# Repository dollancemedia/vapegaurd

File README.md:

# VapeGuard - Real-time Vape Detection System

A comprehensive IoT-based vape detection system using ESP32-C6, machine learning, and real-time monitoring.

## 🏗️ Architecture

```
┌─────────────┐    WiFi     ┌─────────────┐    HTTP/WS   ┌─────────────┐
│   ESP32-C6  │ ──────────► │   Backend   │ ────────────► │  Frontend   │
│   Sensors   │             │  (FastAPI)  │              │   (React)   │
└─────────────┘             └─────────────┘              └─────────────┘
                                    │
                                    ▼
                            ┌─────────────┐
                            │  MongoDB    │
                            │   Atlas     │
                            └─────────────┘
                                    │
                                    ▼
                            ┌─────────────┐
                            │  XGBoost    │
                            │ ML Model    │
                            └─────────────┘
```

## 🚀 Features

### Hardware (ESP32-C6)
- **Multi-sensor Detection**: MQ-2 smoke sensor, DHT22 temperature/humidity, air quality sensor
- **WiFi Connectivity**: Real-time data transmission
- **Local Alerts**: LED and buzzer notifications
- **Zigbee Ready**: ESP32-C6 supports Zigbee mesh networking (future feature)
- **Low Power**: Optimized for continuous operation

### Backend (FastAPI + MongoDB)
- **Real-time API**: RESTful endpoints for sensor data
- **Machine Learning**: XGBoost model for vape detection
- **Data Storage**: MongoDB Atlas for scalable data storage
- **WebSocket Support**: Real-time updates to frontend
- **Vercel Deployment**: Serverless deployment ready

### Frontend (React)
- **Real-time Dashboard**: Live sensor readings and alerts
- **Device Management**: Monitor and control ESP32 devices
- **Event History**: Track and analyze detection events
- **Responsive Design**: Works on desktop and mobile
- **Vercel Deployment**: Static site deployment ready

### Machine Learning
- **XGBoost Model**: High-accuracy vape detection
- **Feature Engineering**: Advanced sensor data processing
- **Real-time Inference**: Sub-second prediction times
- **Confidence Scoring**: Reliability metrics for each prediction

## 📁 Project Structure

```
vape-project/
├── backend/                 # FastAPI backend
│   ├── app/
│   │   ├── main.py         # FastAPI application
│   │   ├── config.py       # Configuration settings
│   │   ├── models/         # Data models
│   │   ├── routers/        # API endpoints
│   │   └── ml/             # Machine learning models
│   └── requirements.txt    # Python dependencies
├── frontend/               # React frontend
│   ├── src/
│   │   ├── components/     # React components
│   │   ├── pages/          # Page components
│   │   ├── services/       # API services
│   │   └── App.js          # Main application
│   ├── public/             # Static assets
│   └── package.json        # Node.js dependencies
├── esp32_vape_sensor/      # ESP32-C6 Arduino code
│   └── esp32_vape_sensor.ino
├── vercel.json             # Vercel deployment config
├── DEPLOYMENT_GUIDE.md     # Detailed deployment instructions
└── README.md               # This file
```

## 🛠️ Quick Start & Run Commands

### Prerequisites
- Node.js 16+ and npm
- Python 3.8+
- Arduino IDE with ESP32 support
- MongoDB (Running locally or via Atlas)

### 1. Start the Database
Ensure MongoDB is running.
- **Windows Service**: Usually runs automatically.
- **Manual**: Run `mongod` in a separate terminal.

### 2. Start the Backend
The backend **must** listen on `0.0.0.0` to accept connections from the ESP32.

```powershell
cd backend
python -m uvicorn app.main:app --reload --host 0.0.0.0 --port 8000
```
*   **Success Indicator**: Logs show `Uvicorn running on http://0.0.0.0:8000`.

### 3. Start the Frontend
Open a **new terminal**.

```powershell
cd frontend
$env:PORT=3002; npm start
```
*   **Success Indicator**: Browser opens to `http://localhost:3002`.

### 4. Power the ESP32
Plug in your ESP32. It is pre-configured to connect to your WiFi and send data to `10.0.0.43:8000`.

---

## 🔧 Hardware Setup
1. **Board**: Adafruit ESP32 Feather V2
2. **Connections**:
   - PMS5003 TX → ESP32 RX (GPIO 16)
   - PMS5003 RX → ESP32 TX (GPIO 17)
   - Power & Ground

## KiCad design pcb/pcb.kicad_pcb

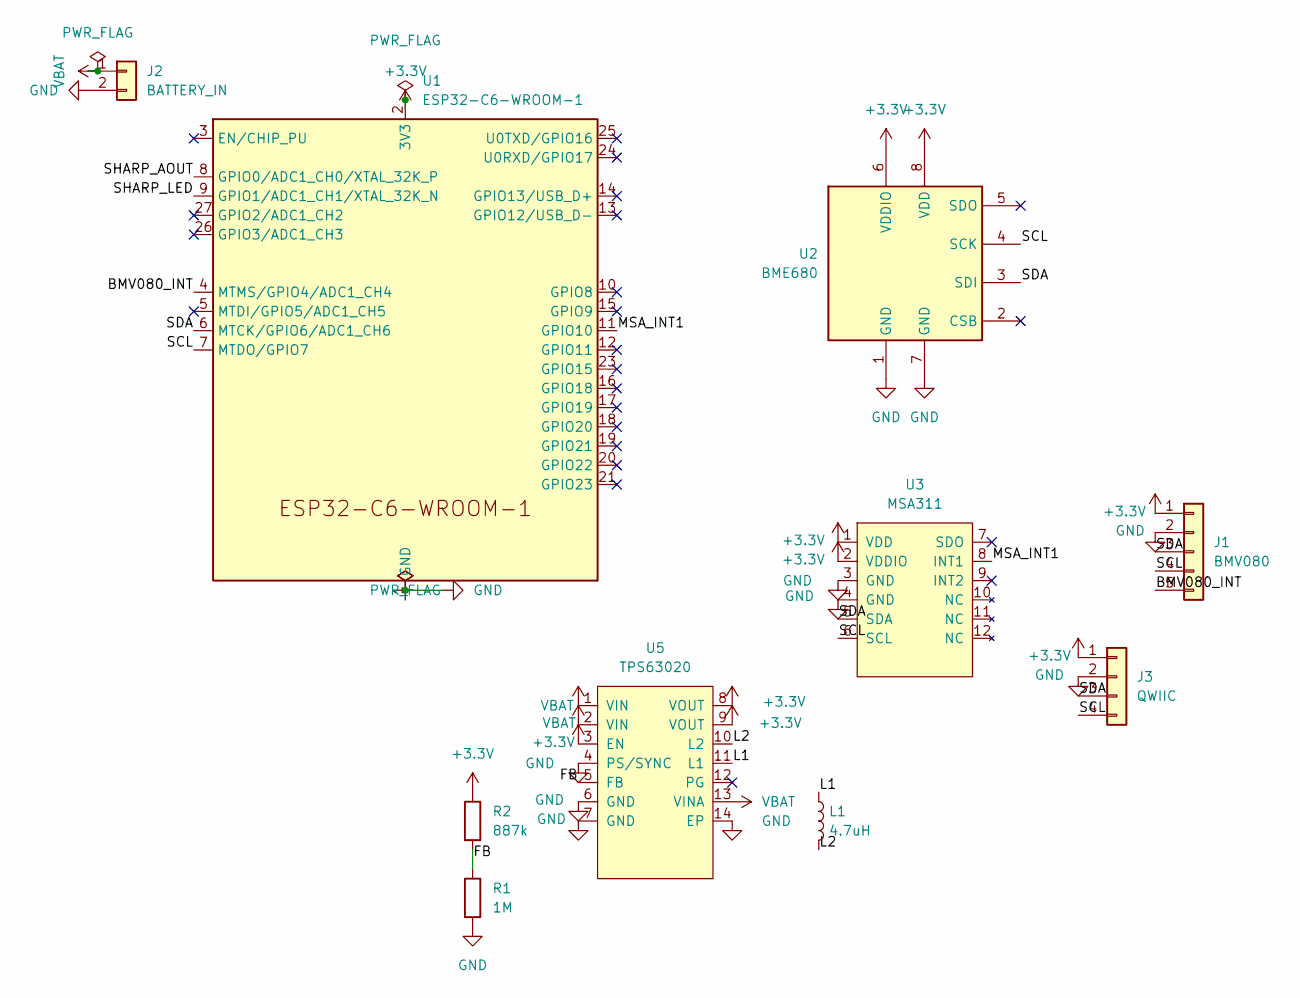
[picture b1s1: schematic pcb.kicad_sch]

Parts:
J1: BMV080; PinHeader_1x05_P2.54mm_Vertical
J2: BATTERY_IN; JST_PH_B2B-PH-K_1x02_P2.00mm_Vertical
J3: QWIIC; JST_SH_SM04B-SRSS-TB_1x04-1MP_P1.00mm_Horizontal
L1: 4.7uH; L_0402_1005Metric
R1: 1M; R_0402_1005Metric
R2: 887k; R_0402_1005Metric
U1: ESP32-C6-WROOM-1
U2: BME680; Bosch_LGA-8_3x3mm_P0.8mm_ClockwisePinNumbering
U3: MSA311; LGA-12_2x2mm_P0.5mm
U5: TPS63020; IC_TPS63020DSJT

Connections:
+3.3V: J1.1, J3.1, R2.1, U1.2 (3V3), U2.6 (VDDIO), U2.8 (VDD), U3.1 (VDD), U3.2 (VDDIO), U5.3 (EN), U5.8 (VOUT), U5.9 (VOUT)
/BMV080_INT: J1.5, U1.4 (MTMS/GPIO4/ADC1_CH4)
/FB: R1.1, R2.2, U5.5 (FB)
/L1: L1.1, U5.11 (L1)
/L2: L1.2, U5.10 (L2)
/MSA_INT1: U1.11 (GPIO10), U3.8 (INT1)
/SCL: J1.4, J3.4, U1.7 (MTDO/GPIO7), U2.4 (SCK), U3.6 (SCL)
/SDA: J1.3, J3.3, U1.6 (MTCK/GPIO6/ADC1_CH6), U2.3 (SDI), U3.5 (SDA)
/SHARP_AOUT: U1.8 (GPIO0/ADC1_CH0/XTAL_32K_P)
/SHARP_LED: U1.9 (GPIO1/ADC1_CH1/XTAL_32K_N)
GND: J1.2, J2.2, J3.2, R1.2, U1.1 (GND), U1.28 (GND), U1.29 (GND), U2.1 (GND), U2.7 (GND), U3.3 (GND), U3.4 (GND), U5.4 (PS/SYNC), U5.6 (GND), U5.7 (GND), U5.14 (EP)
VBAT: J2.1, U5.1 (VIN), U5.2 (VIN), U5.13 (VINA)

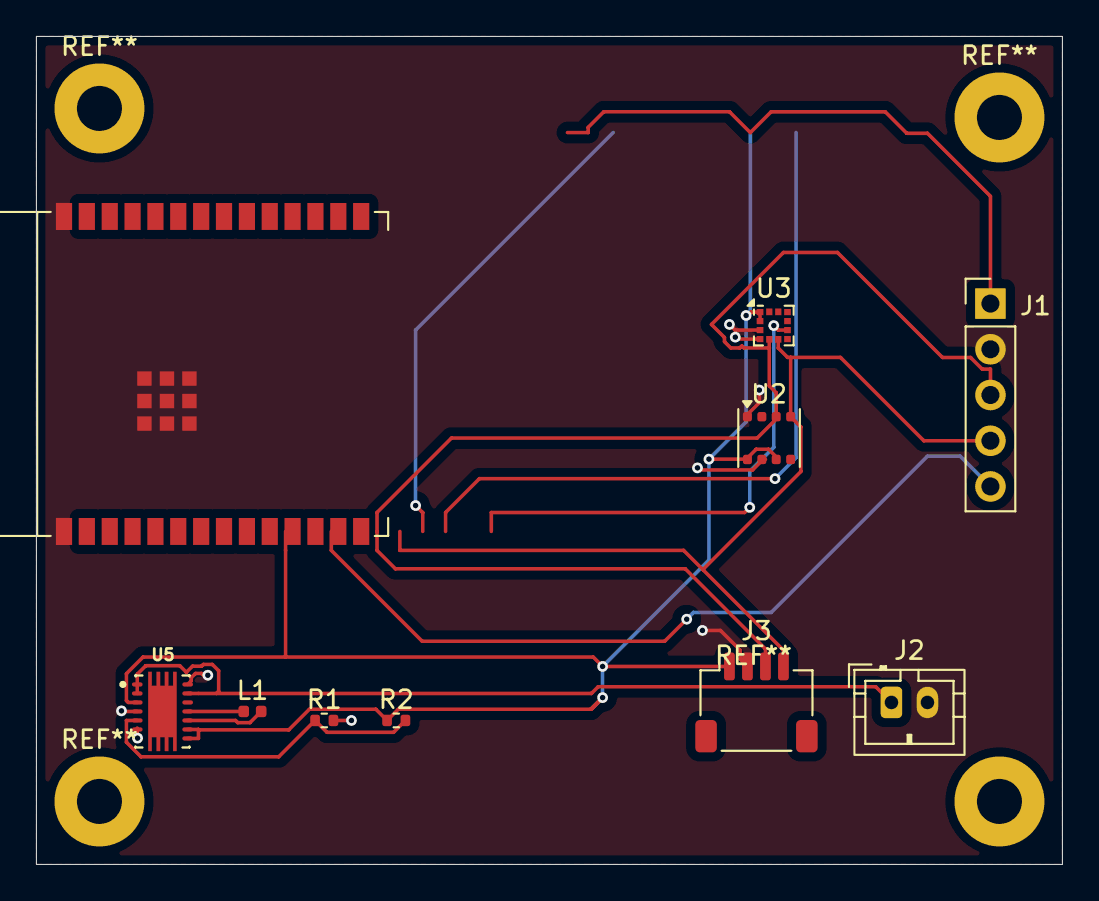
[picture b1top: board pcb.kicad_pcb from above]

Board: 2 copper layers, 57.0 x 46.0 mm, 10 parts (0 on the bottom side), 10 nets.

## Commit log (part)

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2025-07-31 second commit
2025-08-01 Archive old Express backend
2025-08-03 Fix model dump path and add serialized model
2025-08-04 Fix API port discrepancy between frontend and backend
2025-08-04 Add device summary endpoint and event feedback route
2025-08-24 Prepare for Vercel deployment: Add vercel.json, update frontend for env vars, add deployment scripts
2025-08-24 Fix MongoDB environment variables in vercel.json for deployment
2025-08-24 Fix ESLint warnings and errors - remove unused variables and imports, fix missing dependencies
2025-08-24 Fix Vercel deployment configuration - remove duplicate vercel.json and fix routing
2025-08-29 Update ESP32 vape sensor project with PMS5003 integration, hardware guides, and Arduino tools
2025-12-28 feat: prepare for deployment - backend auth, frontend clerk integration, and vercel config
2025-12-28 Fix: Add vercel.json and rename proxy.ts to middleware.ts
2025-12-30 chore: prepare backend for deployment and update config
2025-12-30 fix: delay db connection in train_model.py to prevent import-time crash
2025-12-30 update landingpage submodule to include login redirect
2025-12-30 Update dashboard to dynamically load campus map based on user (wwhs/irvington)
2025-12-30 Remove Trae Solo watermark and update login redirect
2025-12-31 Update DeviceMap with organization-based map selection and asset reorganization
2025-12-31 Update project files: Sync local changes to remote
2025-12-31 Update CORS to include Railway production domain
2025-12-31 fix: make MONGODB_URI optional to prevent startup crash
2025-12-31 chore: update backend config and add nixpacks.toml
2025-12-31 Update repository: Flatten landingpage submodule and remove debris
2025-12-31 feat: update favicon to tablogo.png
2025-12-31 feat: enhance ui with smoother animations and updated content
2026-01-01 Update model_config and esp32_vape_sensor sketch
2026-01-01 Update esp32_vape_sensor_002 sketch
2026-01-01 Fix Dashboard: Add missing useAuth import and correct DeviceMap data source
2026-01-01 Refactor Dashboard WebSocket connection to prevent infinite reconnection loop
2026-01-01 Fix WebSocket infinite loop by memoizing entire options object including protocols
2026-01-01 Apply user fixes to useWebSocket hook
2026-01-01 pls work bro
2026-01-01 pls work 2x
2026-01-01 Update mobile dashboard: Full-width map, remove footer, improve hooks compliance
2026-01-01 Resolve merge conflicts and apply mobile dashboard updates
2026-01-01 Refactor school selection and map image logic
    Updated components to use organization name instead of slug for school selection and map image paths. DeviceMap now preloads map images and falls back to a default if not found. Device service logic 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
2026-01-04 Add ESP32-C6 vape sensor firmware and fix device name logic
    Added initial firmware for the ESP32-C6 vape detection sensor, supporting WiFi setup, BME680, PMS5003, and microphone input, with data upload to a FastAPI backend. Also fixed device name selection lo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
2026-01-04 Refactor device summary query and code style cleanup
    Updated backend device summary logic to query 'devices' collection by 'org_id' and use 'device_id' instead of 'sensors' and 'name'. Cleaned up code style and formatting in vape_sensor_bluetooth.ino, 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
2026-01-18 feat: update project setup and device management
2026-01-19 fix eslint errors for vercel deployment
2026-01-19 Refactor WiFi provisioning and HTTP client logic
    Replaces HTTPClient with esp_http_client for improved HTTPS support and efficiency. Adds BLE-based WiFi provisioning using NimBLE, persistent credential storage with Preferences, and factory reset lo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
2026-01-19 Update for AddDevices to filter bluetooth devices list
2026-01-19 Improve BLE provisioning reliability and logging
    Added debug logging to BLE characteristic write callbacks in both ESP32 firmware files. Updated BLE characteristics to use both WRITE and WRITE_NR properties and refactored callback assignment to use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
2026-01-19 Finally works
    Yo ts mad tuff, it works v well now
2026-01-19 use name instead of id
2026-01-21 Add DELETE /devices/{device_id} endpoint to backend
2026-01-21 Bump API version to 1.0.1 to trigger deployment
2026-01-21 Improve error handling for device deletion in frontend
2026-01-22 Fix sensor discovery by org ID and prevent cross-site notifications
2026-01-22 Update PWA icons to tablogo and fix AddDeviceModal org ID
2026-01-22 Fix NotificationController dependency array for school
2026-01-22 Update PWA icon to applogo.png while keeping tablogo.png for favicon
2026-01-22 Add applogo.png to frontend/public for PWA icon
2026-01-22 Fix organization name check to lowercase 'admin'
    Updated the Devices page to check for 'admin' in lowercase when determining the school variable. This ensures consistency with organization slugs and prevents case sensitivity issues.
2026-01-22 Fix notification acknowledgement to mute only the specific sensor for 10 minutes
2026-01-25 Fix unused variable error in SchoolNotificationSystem.js
2026-02-01 Load classifications from external file in model scripts
    Added 'classifications.txt' to store classification labels and updated all model training scripts to read classifications from this file. This centralizes label management and improves maintainabilit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
2026-02-01 Fix classification file path handling in model scripts
    Updated all backend model training scripts to dynamically determine the path to 'classifications.txt', ensuring compatibility whether the script is run from the project root or the backend directory.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
2026-02-01 Generalize class handling for multi-class support
    Refactored all train_model scripts to use a new check_type() function for mapping class labels to indices, replacing hardcoded binary logic. Updated dataset statistics and prediction output to suppor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
2026-02-01 Add dynamic classification support and improve event handling
    Introduces dynamic loading of classification labels from a file in both backend and research modules, replacing hardcoded class names. Updates event handling logic in backend and frontend tables to d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
2026-02-02 Update vape detection models and ensemble logic
2026-02-02 update shi
2026-02-02 Load class order from classifications.txt file
    Refactored class_config.py to dynamically load class names from classifications.txt instead of hardcoding them. Added a fallback to default classes if the file is missing. Updated classifications.txt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
2026-02-02 Lower uncertainty thresholds to force predictions
2026-02-02 Replace SVC with KNN in ensemble
2026-02-04 Fix device offline status by updating last_seen on sample ingest
2026-02-04 Update DeviceDetailPanel to show calibrating/suspected states and logs
2026-02-04 Fix unused variables in DeviceDetailPanel
2026-02-04 Fix frozen dashboard (WS token) and normal status (Absolute PM2.5 threshold)
2026-02-04 Revert absolute threshold in detector logic
2026-02-04 bruh
2026-02-04 asdijs
2026-02-04 Fix device summary logic to show live data and handle missing events
2026-02-09 Smooth scroll, update contact & preload video
    Add a smooth scrolling handler in Navbar that prevents default anchor behavior, scrolls to section targets with an 80px offset (navbar height), and closes the mobile menu. Wire the handler to both de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
2026-02-12 Add recalibration, timestamps, and UI state fixes
    Detector: add _iso_utc helper and include ISO UTC timestamps for events/decisions; improve default state initialization for new devices. Routers: add POST /{device_id}/recalibrate to force recalibrat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
2026-02-12 Add WARMUP startup state and UI support
    Introduce a new WARMUP startup phase before calibration: add WARMUP_DURATION_SEC and reduce CALIBRATION_DURATION_SEC to 60s in config. Backend Detector: add robust datetime parsing (_parse_state_dt),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
2026-02-12 Reduce warmup and extend device state fields
    Lower WARMUP_DURATION_SEC from 120 to 90 seconds and extend the device state payload with warmup_start, calibration_start, and event_id. Initialize these new keys in the default state and add parsing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
2026-02-12 Use negative fallbacks for top_prob in confidence
    Distinguish missing top_prob from an explicit zero by changing the fallback values used when computing confidence from 0 to small negative values. This ensures absent probabilities are treated differ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
2026-02-12 Revert "Railway didn't pick up last change"
    This reverts commit 03226d344198c204b5e896a81ae450ef54ff4b95.
2026-02-12 Revert "Use negative fallbacks for top_prob in confidence"
    This reverts commit 99d33474ff36a00fe1ead39124a1d2b9d44d270c.
2026-02-13 Persist sensor baselines and add cooldown UI
    Freeze and persist calibrated baselines, surface them to the API and UI, and add COOLDOWN handling + robustness fixes.
    Changes:
    - Detector: when calibration completes, store frozen baselines (pm25, pm10, humidity, temperature, gas_resistance) and mark status IDLE. In IDLE, use frozen baseline for delta checks (do not roll ewm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
    - State manager: add baseline_* fields to device state defaults and load them from storage.
    - Routers/sensors: wrap detector.process_sample in try/except to keep raw streaming alive if detector logic fails; use a server timestamp for live UI while preserving device timestamp
2026-02-15 Merge and sanitize device sensor updates
    Add pickDefined/mergeDefined helpers and update device update logic to only apply defined/non-null fields. useDevices updateDeviceStatus now merges sensorData and location without overwriting existin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
2026-02-15 Add Vercel build/install and output config
    Add explicit Vercel settings to frontend/vercel.json: set "framework" to null and specify "installCommand": "npm install", "buildCommand": "npm run build", and "outputDirectory": "build" so Vercel ca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
2026-02-18 Refactor updateDeviceStatus merge logic
    Replace nested ternary mapping with clearer early-return mapping and simplify merging logic. Sensor data is now deep-merged via mergeDefined(device.sensorData, updates.sensorData) to preserve existin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
2026-02-19 Add deterministic training dataset builder
    Introduce a dataset builder script (backend/build_training_dataset.py) that loads event labels, fetches raw samples from MongoDB, infers event end-times when missing, generates overlapping windows, c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
2026-02-21 Enhance detection logic & config; add docs
    Add CLAUDE.md and .claude settings; overhaul detector and config to improve detection quality. Changes include: added slope-based trigger (uses prev_pm25 and prev_ts), richer logging, trigger_reason 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
2026-02-21 Lazy-import retrain module; UI assets cleanup
    Make train_model import lazy in admin retrain endpoint and return a 501 if the module isn't available in the deployment (prevents import errors in production). Add local permission for Bash(tail:*) i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
2026-02-22 Refactor device detail UI & tweak event handling
    Frontend: Major refactor of DeviceDetailPanel into smaller reusable pieces and a new MobileDeviceDetail view (StatusBanner, LiveReadings, SensorTrends, RecentEvents, EditModal). Chart logic extracted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
    Backend: lowered COOLDOWN_SEC from 90s to 20s in config and expanded events router get_events to defau
2026-02-22 Normalize event type and confidence sources
    Prefer backend-specific fields when normalizing events: check top_class and status for event type before falling back to legacy fields, and use top_prob as a confidence source if present. Also docume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
2026-03-05 haa
    type shit
2026-04-01 Format ring percentage to two decimals
    Update Ring component to render the percentage with value.toFixed(2) in the SVG text element, ensuring the displayed value always shows two decimal places (e.g. 12.34%) for consistent UI formatting.
